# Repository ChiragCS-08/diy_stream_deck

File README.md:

# diy_stream_deck
Open-source, low-cost Stream Deck alternative built on the RP2040 (MicroPython). Features a TCA9548A I²C multiplexer driving 6 OLED displays for dynamic key icons, USB HID macro execution, and a fully custom KiCad PCB with zero-violation ERC. An affordable, hackable input handler for streamers, devs, and productivity workflows.

Programmable Input Handler — a DIY, fully customizable macro keypad and Stream Deck alternative, designed as a low-cost, open-source answer to expensive commercial input devices.
Built around an RP2040 microcontroller running MicroPython, the device uses a TCA9548A I²C multiplexer to drive 6 independent OLED displays, giving each key a dynamic, reprogrammable icon. It acts as a USB HID device, sending keyboard shortcuts and macros to trigger actions in tools like OBS Studio, VS Code, and Spotify.

=======

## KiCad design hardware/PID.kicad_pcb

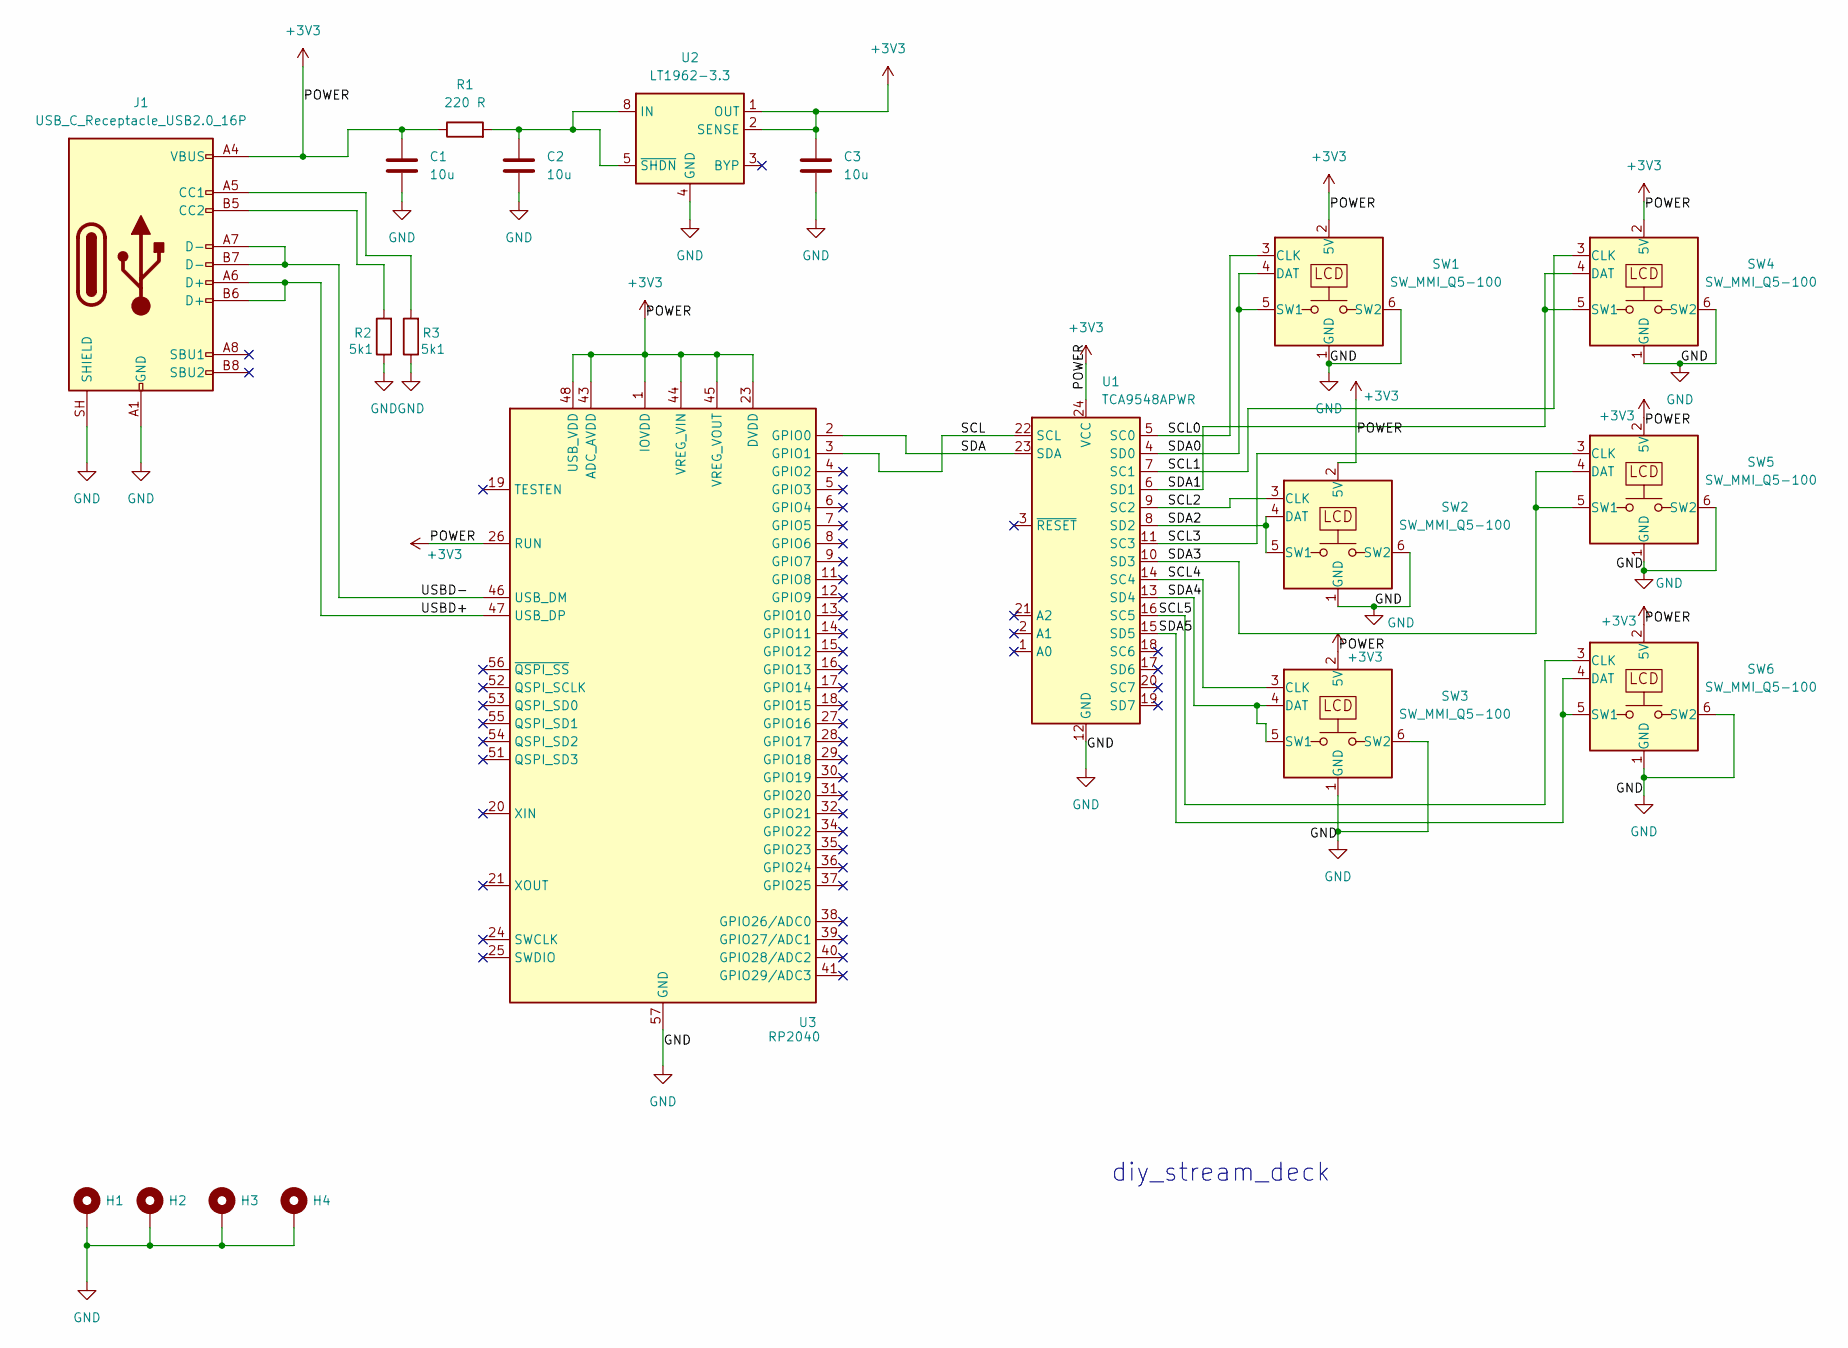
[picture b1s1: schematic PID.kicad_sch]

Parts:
C1: 10u; C_0402_1005Metric_Pad0.74x0.62mm_HandSolder
C2, C3: 10u; C_0201_0603Metric_Pad0.64x0.40mm_HandSolder
H1, H2, H3, H4: MountingHole_Pad; MountingHole_3mm_Pad_TopBottom
J1: USB_C_Receptacle_USB2.0_16P; USB_C_Receptacle_GCT_USB4085
R1: 220 R; R_01005_0402Metric
R2, R3: 5k1; R_01005_0402Metric
SW1, SW2, SW3, SW4, SW5, SW6: SW_MMI_Q5-100; SW_PUSH_LCD_E3_SAxxxx_SocketPins
U1: TCA9548APWR; TSSOP-24_4.4x7.8mm_P0.65mm
U2: LT1962-3.3; MSOP-8_3x3mm_P0.65mm
U3: RP2040; QFN-56-1EP_7x7mm_P0.4mm_EP3.2x3.2mm

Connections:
+3V3: C1.1, C3.1, J1.A4 (VBUS), J1.A9 (VBUS), J1.B4 (VBUS), J1.B9 (VBUS), R1.1, SW1.2 (5V), SW2.2 (5V), SW3.2 (5V), SW4.2 (5V), SW5.2 (5V), SW6.2 (5V), U1.24 (VCC), U2.1 (OUT), U2.2 (SENSE), U3.1 (IOVDD), U3.10 (IOVDD), U3.22 (IOVDD), U3.23 (DVDD), U3.26 (RUN), U3.33 (IOVDD), U3.42 (IOVDD), U3.43 (ADC_AVDD), U3.44 (VREG_VIN), U3.45 (VREG_VOUT), U3.48 (USB_VDD), U3.49 (IOVDD), U3.50 (DVDD)
/SCL: U1.22 (SCL), U3.3 (GPIO1)
/SCL0: SW1.3 (CLK), U1.5 (SC0)
/SCL1: SW4.3 (CLK), U1.7 (SC1)
/SCL2: SW2.3 (CLK), U1.9 (SC2)
/SCL3: SW5.3 (CLK), U1.11 (SC3)
/SCL4: SW3.3 (CLK), U1.14 (SC4)
/SCL5: SW6.3 (CLK), U1.16 (SC5)
/SDA: U1.23 (SDA), U3.2 (GPIO0)
/SDA0: SW1.4 (DAT), SW1.5 (SW1), U1.4 (SD0)
/SDA1: SW4.4 (DAT), SW4.5 (SW1), U1.6 (SD1)
/SDA2: SW2.4 (DAT), SW2.5 (SW1), U1.8 (SD2)
/SDA3: SW5.4 (DAT), SW5.5 (SW1), U1.10 (SD3)
/SDA4: SW3.4 (DAT), SW3.5 (SW1), U1.13 (SD4)
/SDA5: SW6.4 (DAT), SW6.5 (SW1), U1.15 (SD5)
/USBD+: J1.A6 (D+), J1.B6 (D+), U3.47 (USB_DP)
/USBD-: J1.A7 (D-), J1.B7 (D-), U3.46 (USB_DM)
GND: C1.2, C2.2, C3.2, H1.1 (1_1), H2.1 (1_1), H3.1 (1_1), H4.1 (1_1), J1.A1 (GND), J1.A12 (GND), J1.B1 (GND), J1.B12 (GND), J1.SH (SHIELD), R2.1, R3.1, SW1.1 (GND), SW1.6 (SW2), SW2.1 (GND), SW2.6 (SW2), SW3.1 (GND), SW3.6 (SW2), SW4.1 (GND), SW4.6 (SW2), SW5.1 (GND), SW5.6 (SW2), SW6.1 (GND), SW6.6 (SW2), U1.12 (GND), U2.4 (GND), U3.57 (GND)
unnamed: J1.A5 (CC1), R3.2
unnamed: J1.B5 (CC2), R2.2
unnamed: C2.1, R1.2, U2.5 (~SHDN), U2.8 (IN)

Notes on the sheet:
diy_stream_deck

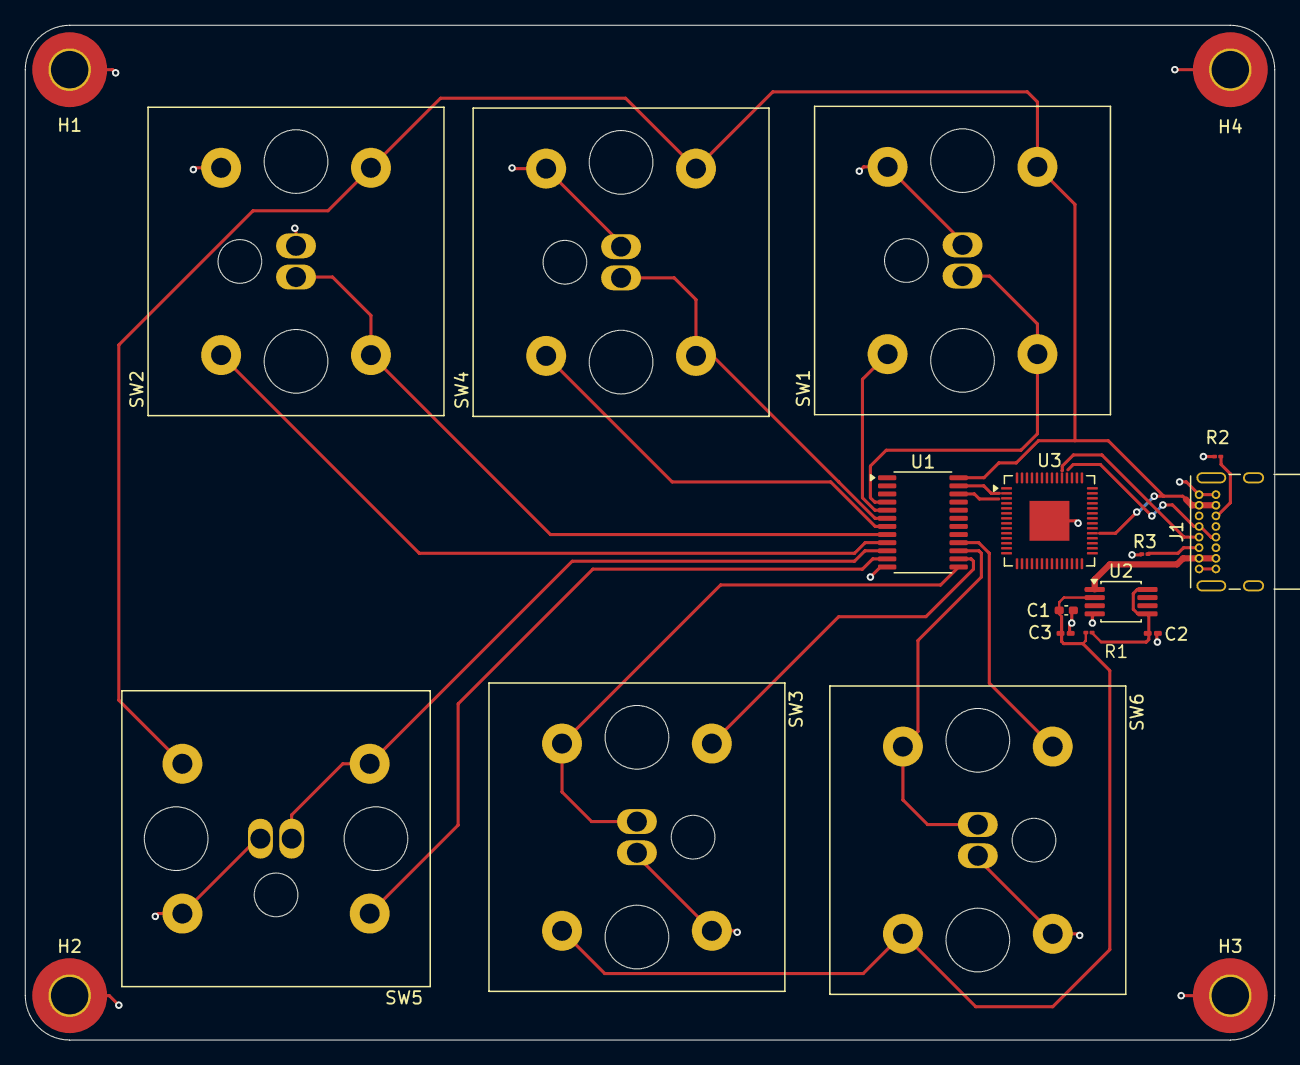
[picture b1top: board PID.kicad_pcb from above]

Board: 2 copper layers, 100.1 x 81.3 mm, 20 parts (0 on the bottom side), 21 nets.
